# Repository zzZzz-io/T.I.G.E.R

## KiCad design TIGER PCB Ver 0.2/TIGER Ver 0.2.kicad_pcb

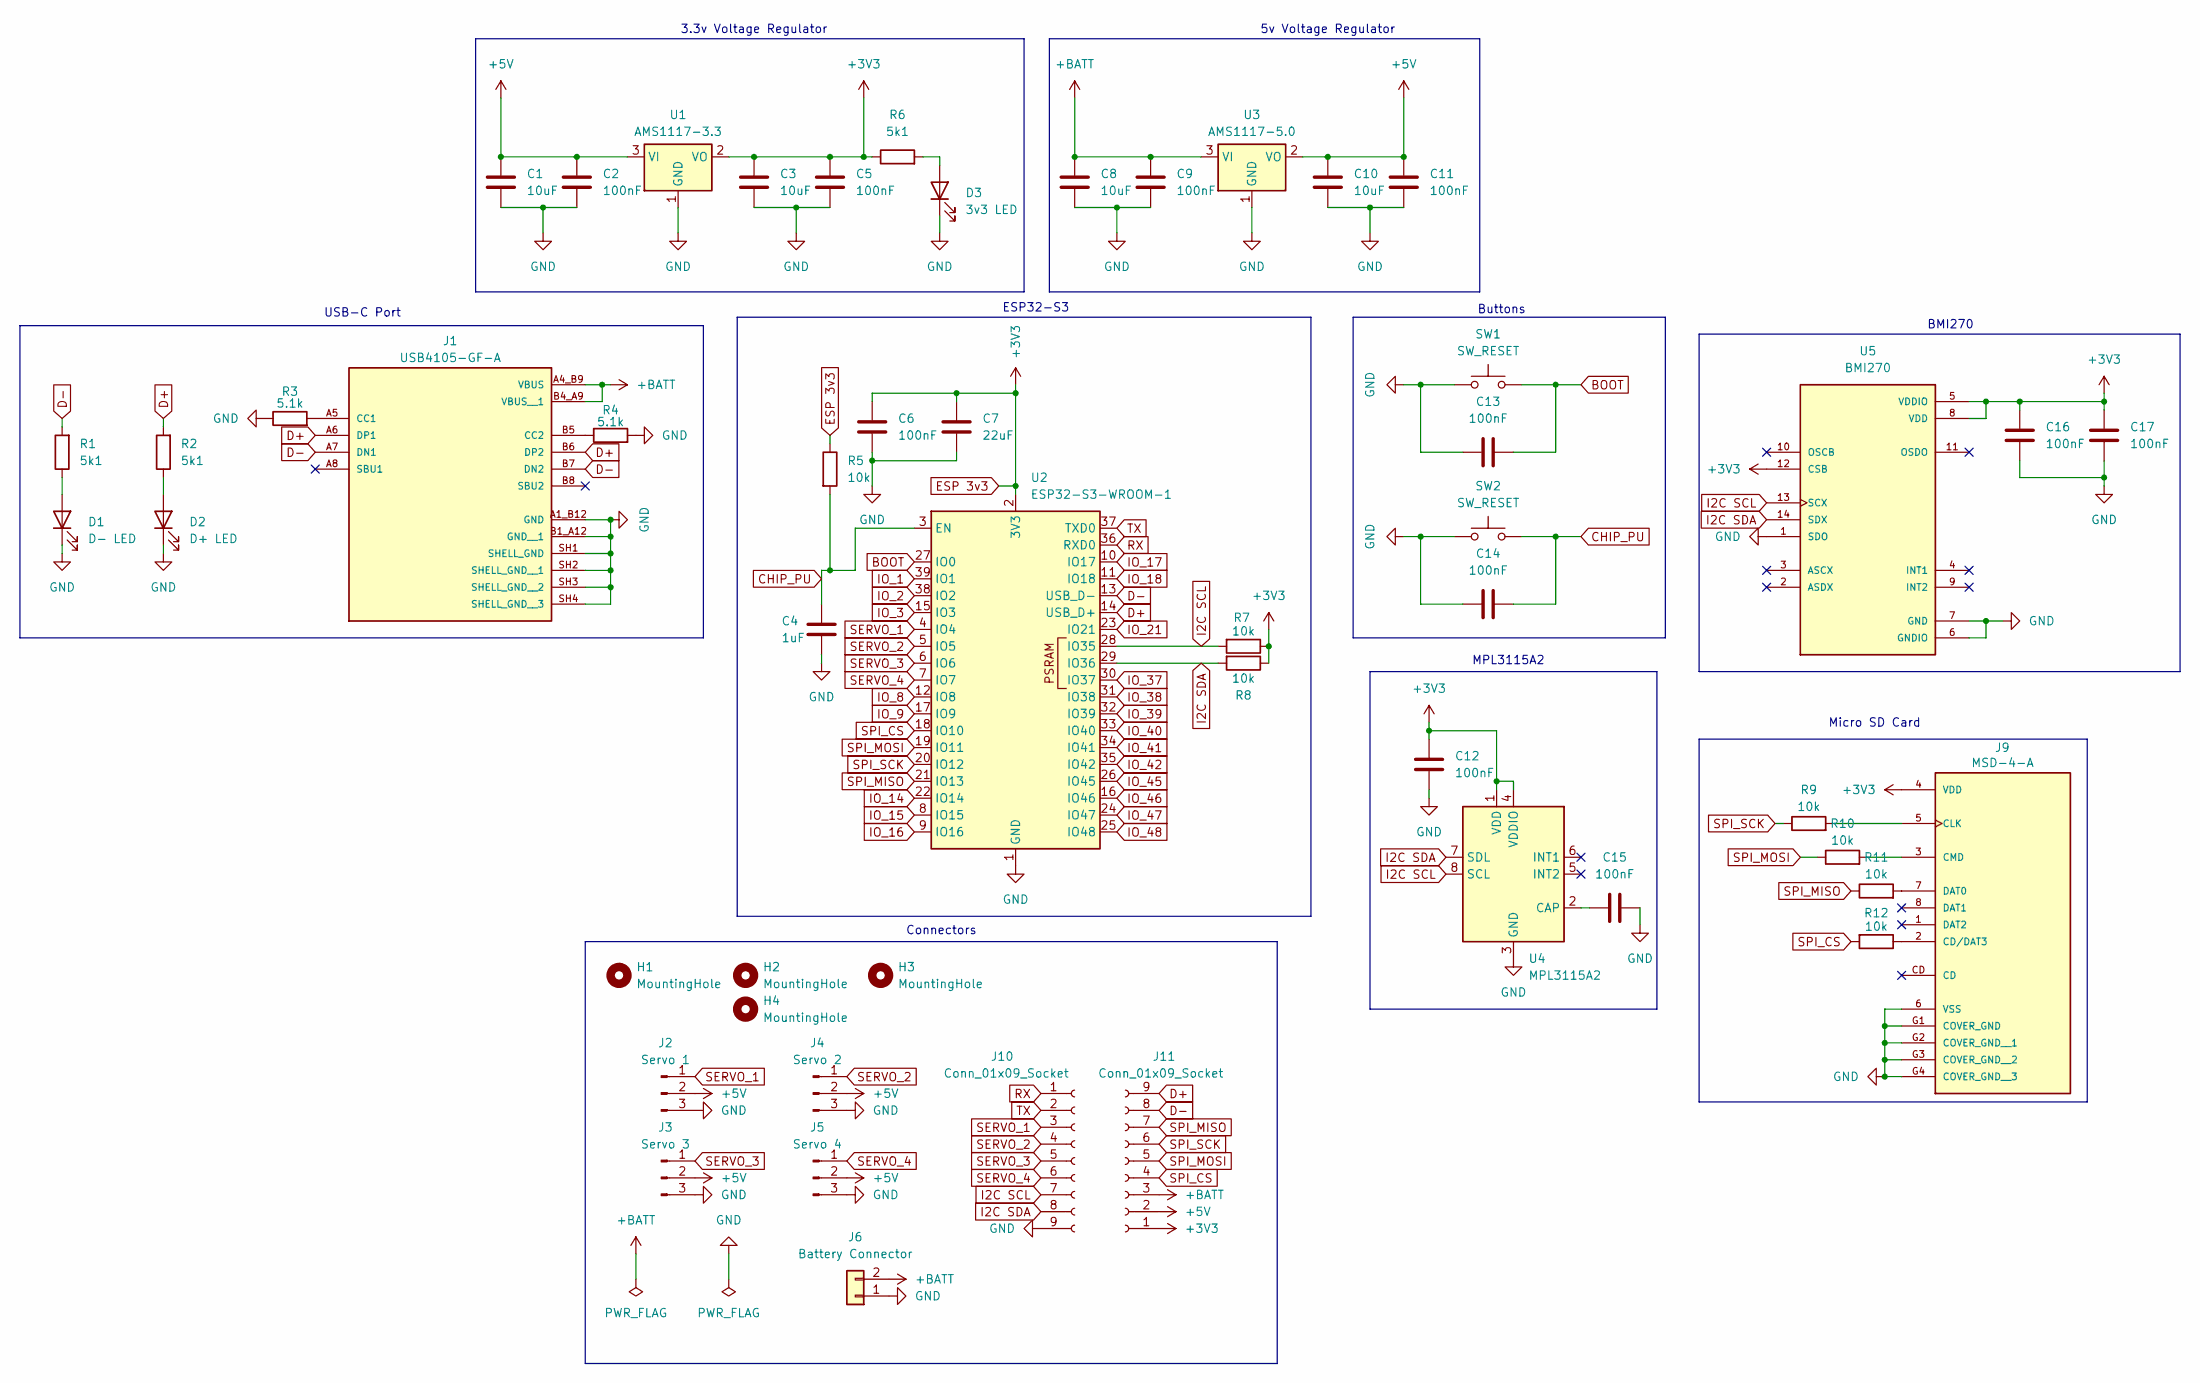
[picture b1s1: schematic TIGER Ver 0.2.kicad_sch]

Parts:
C1, C3, C8, C10: 10uF; C_0603_1608Metric
C2, C5, C6, C9, C11, C12, C13, C14, C15, C16, C17: 100nF; C_0603_1608Metric
C4: 1uF; C_0603_1608Metric
C7: 22uF; C_0603_1608Metric
D1: D- LED; LED_0603_1608Metric
D2: D+ LED; LED_0603_1608Metric
D3: 3v3 LED; LED_0603_1608Metric
H1, H2, H3, H4: MountingHole; MountingHole_3.2mm_M3
J1: USB4105-GF-A; GCT_USB4105-GF-A; PARTREV B4
J2: Servo 1; JST_PH_B3B-PH-K_1x03_P2.00mm_Vertical
J3: Servo 3; JST_PH_B3B-PH-K_1x03_P2.00mm_Vertical
J4: Servo 2; JST_PH_B3B-PH-K_1x03_P2.00mm_Vertical
J5: Servo 4; JST_PH_B3B-PH-K_1x03_P2.00mm_Vertical
J6: Battery Connector
J9: MSD-4-A; CUI_MSD-4-A; PARTREV 1.0
J10, J11: Conn_01x09_Socket; PinSocket_1x09_P2.54mm_Vertical
R1, R2, R6: 5k1; R_0603_1608Metric
R3, R4: 5.1k; R_0603_1608Metric
R5, R7, R8, R9, R10, R11, R12: 10k; R_0603_1608Metric
SW1, SW2: SW_RESET; SW_PUSH_6mm
U1: AMS1117-3.3; SOT-223-3_TabPin2
U2: ESP32-S3-WROOM-1
U3: AMS1117-5.0; SOT-223-3_TabPin2
U4: MPL3115A2; NXP_LGA-8_3x5mm_P1.25mm_H1.1mm
U5: BMI270; XDCR_BMI270

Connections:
+5V: C1.1, C2.1, C10.1, C11.1, J2.2, J3.2, J4.2, J5.2, J11.2, U1.3 (VI), U3.2 (VO)
+BATT: C8.1, C9.1, J1.A4_B9 (VBUS), J1.B4_A9 (VBUS__1), J6.2, J11.3, U3.3 (VI)
BOOT: C13.1, SW1.2, U2.27 (IO0)
CHIP_PU: C4.1, C14.1, R5.2, SW2.2, U2.3 (EN)
D+: J1.A6 (DP1), J1.B6 (DP2), J11.9, R2.2, U2.14 (USB_D+)
D-: J1.A7 (DN1), J1.B7 (DN2), J11.8, R1.2, U2.13 (USB_D-)
ESP 3v3: C3.1, C5.1, C6.1, C7.1, C12.2, C16.2, C17.1, J9.4 (VDD), J11.1, R5.1, R6.1, R7.1, R8.1, U1.2 (VO), U2.2 (3V3), U4.1 (VDD), U4.4 (VDDIO), U5.5 (VDDIO), U5.8 (VDD), U5.12 (CSB)
GND: C1.2, C2.2, C3.2, C4.2, C5.2, C6.2, C7.2, C8.2, C9.2, C10.2, C11.2, C12.1, C13.2, C14.2, C15.2, C16.1, C17.2, D1.1 (K), D2.1 (K), D3.1 (K), J1.A1_B12 (GND), J1.B1_A12 (GND__1), J1.SH1 (SHELL_GND), J1.SH2 (SHELL_GND__1), J1.SH3 (SHELL_GND__2), J1.SH4 (SHELL_GND__3), J2.3, J3.3, J4.3, J5.3, J6.1, J9.6 (VSS), J9.G1 (COVER_GND), J9.G2 (COVER_GND__1), J9.G3 (COVER_GND__2), J9.G4 (COVER_GND__3), J10.9, R3.1, R4.2, SW1.1, SW2.1, U1.1 (GND), U2.1 (GND), U2.40 (GND), U2.41 (GND), U3.1 (GND), U4.3 (GND), U5.1 (SDO), U5.6 (GNDIO), U5.7 (GND); also elsewhere on the board
I2C SCL: J10.7, R7.2, U2.28 (IO35), U4.8 (SCL), U5.13 (SCX)
I2C SDA: J10.8, R8.2, U2.29 (IO36), U4.7 (SDL), U5.14 (SDX)
IO_1: U2.39 (IO1)
IO_2: U2.38 (IO2)
IO_3: U2.15 (IO3)
IO_8: U2.12 (IO8)
IO_9: U2.17 (IO9)
IO_14: U2.22 (IO14)
IO_15: U2.8 (IO15)
IO_16: U2.9 (IO16)
IO_17: U2.10 (IO17)
IO_18: U2.11 (IO18)
IO_21: U2.23 (IO21)
IO_37: U2.30 (IO37)
IO_38: U2.31 (IO38)
IO_39: U2.32 (IO39)
IO_40: U2.33 (IO40)
IO_41: U2.34 (IO41)
IO_42: U2.35 (IO42)
IO_45: U2.26 (IO45)
IO_46: U2.16 (IO46)
IO_47: U2.24 (IO47)
IO_48: U2.25 (IO48)
unnamed: D1.2 (A), R1.1
unnamed: D2.2 (A), R2.1
unnamed 33: D3.2 (A), R6.2; also elsewhere on the board
unnamed: J1.A5 (CC1), R3.2
unnamed: J1.B5 (CC2), R4.1
unnamed: J9.2 (CD/DAT3), R12.1
unnamed: J9.5 (CLK), R9.2
unnamed: J9.3 (CMD), R10.2
unnamed: J9.7 (DAT0), R11.2
unnamed: C15.1, U4.2 (CAP)
RX: J10.1, U2.36 (RXD0)
SERVO_1: J2.1, J10.3, U2.4 (IO4)
SERVO_2: J4.1, J10.4, U2.5 (IO5)
SERVO_3: J3.1, J10.5, U2.6 (IO6)
SERVO_4: J5.1, J10.6, U2.7 (IO7)
SPI_CS: J11.4, R12.2, U2.18 (IO10)
SPI_MISO: J11.7, R11.1, U2.21 (IO13)
SPI_MOSI: J11.5, R10.1, U2.19 (IO11)
SPI_SCK: J11.6, R9.1, U2.20 (IO12)
TX: J10.2, U2.37 (TXD0)

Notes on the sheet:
Micro SD Card
Buttons
ESP32-S3
USB-C Port
3.3v Voltage Regulator
Connectors
5v Voltage Regulator
MPL3115A2
BMI270

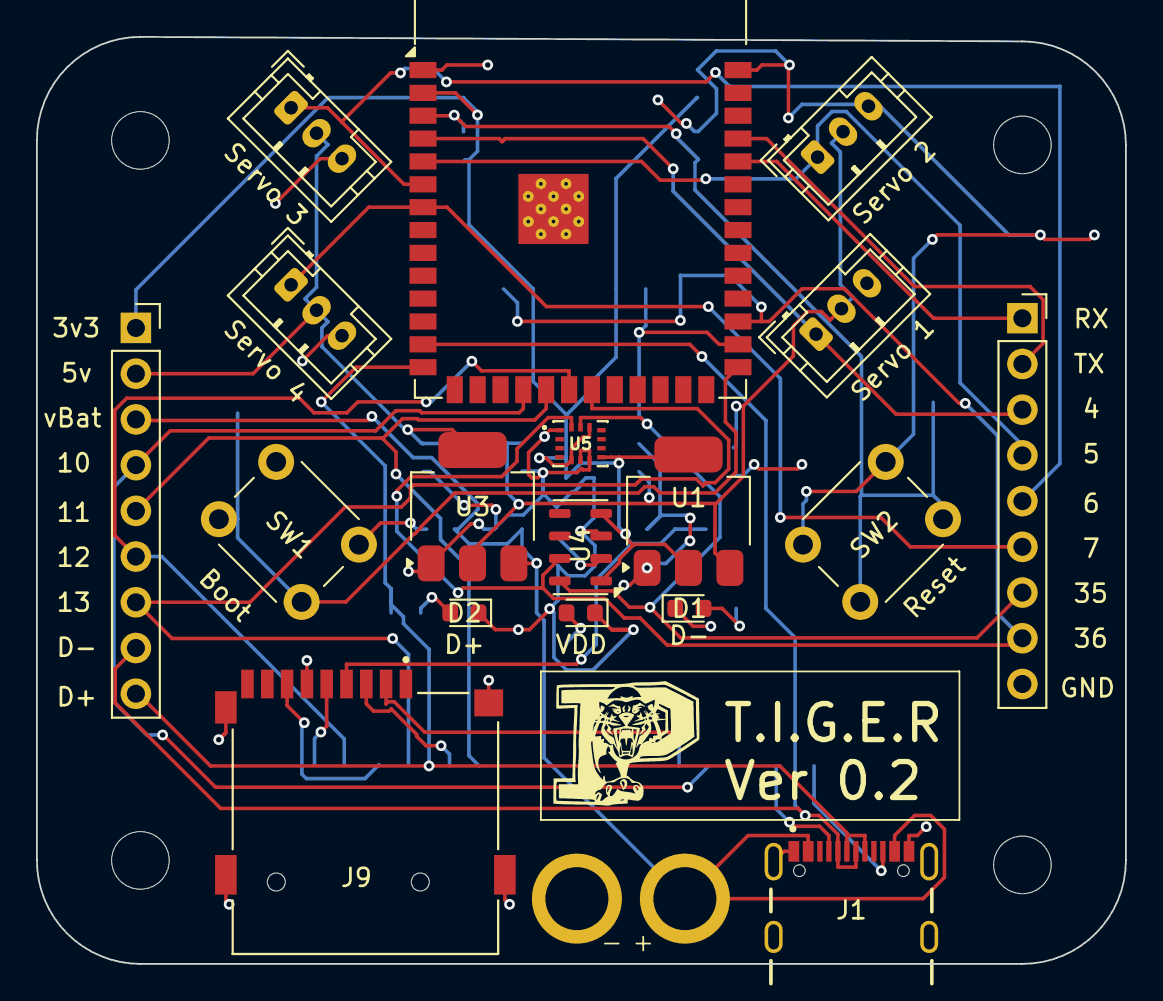
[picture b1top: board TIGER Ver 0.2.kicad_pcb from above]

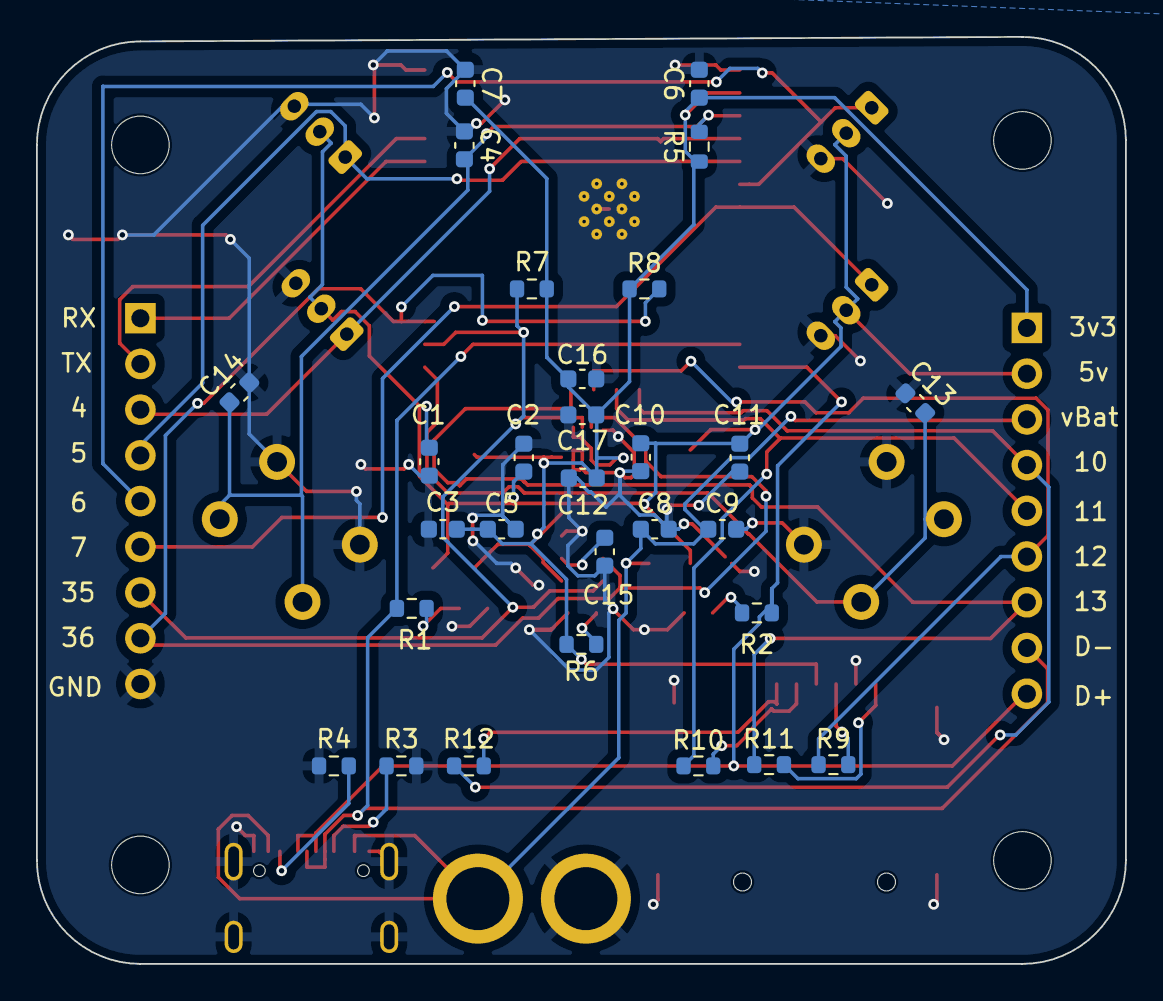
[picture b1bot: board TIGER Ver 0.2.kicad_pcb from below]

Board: 2 copper layers, 60.5 x 51.5 mm, 52 parts (29 on the bottom side), 30 nets.

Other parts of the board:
VDD: 3v3 LED; LED_0603_1608Metric

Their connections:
GND: VDD.1 (K); also elsewhere on the board
unnamed 33: VDD.2 (A); also elsewhere on the board

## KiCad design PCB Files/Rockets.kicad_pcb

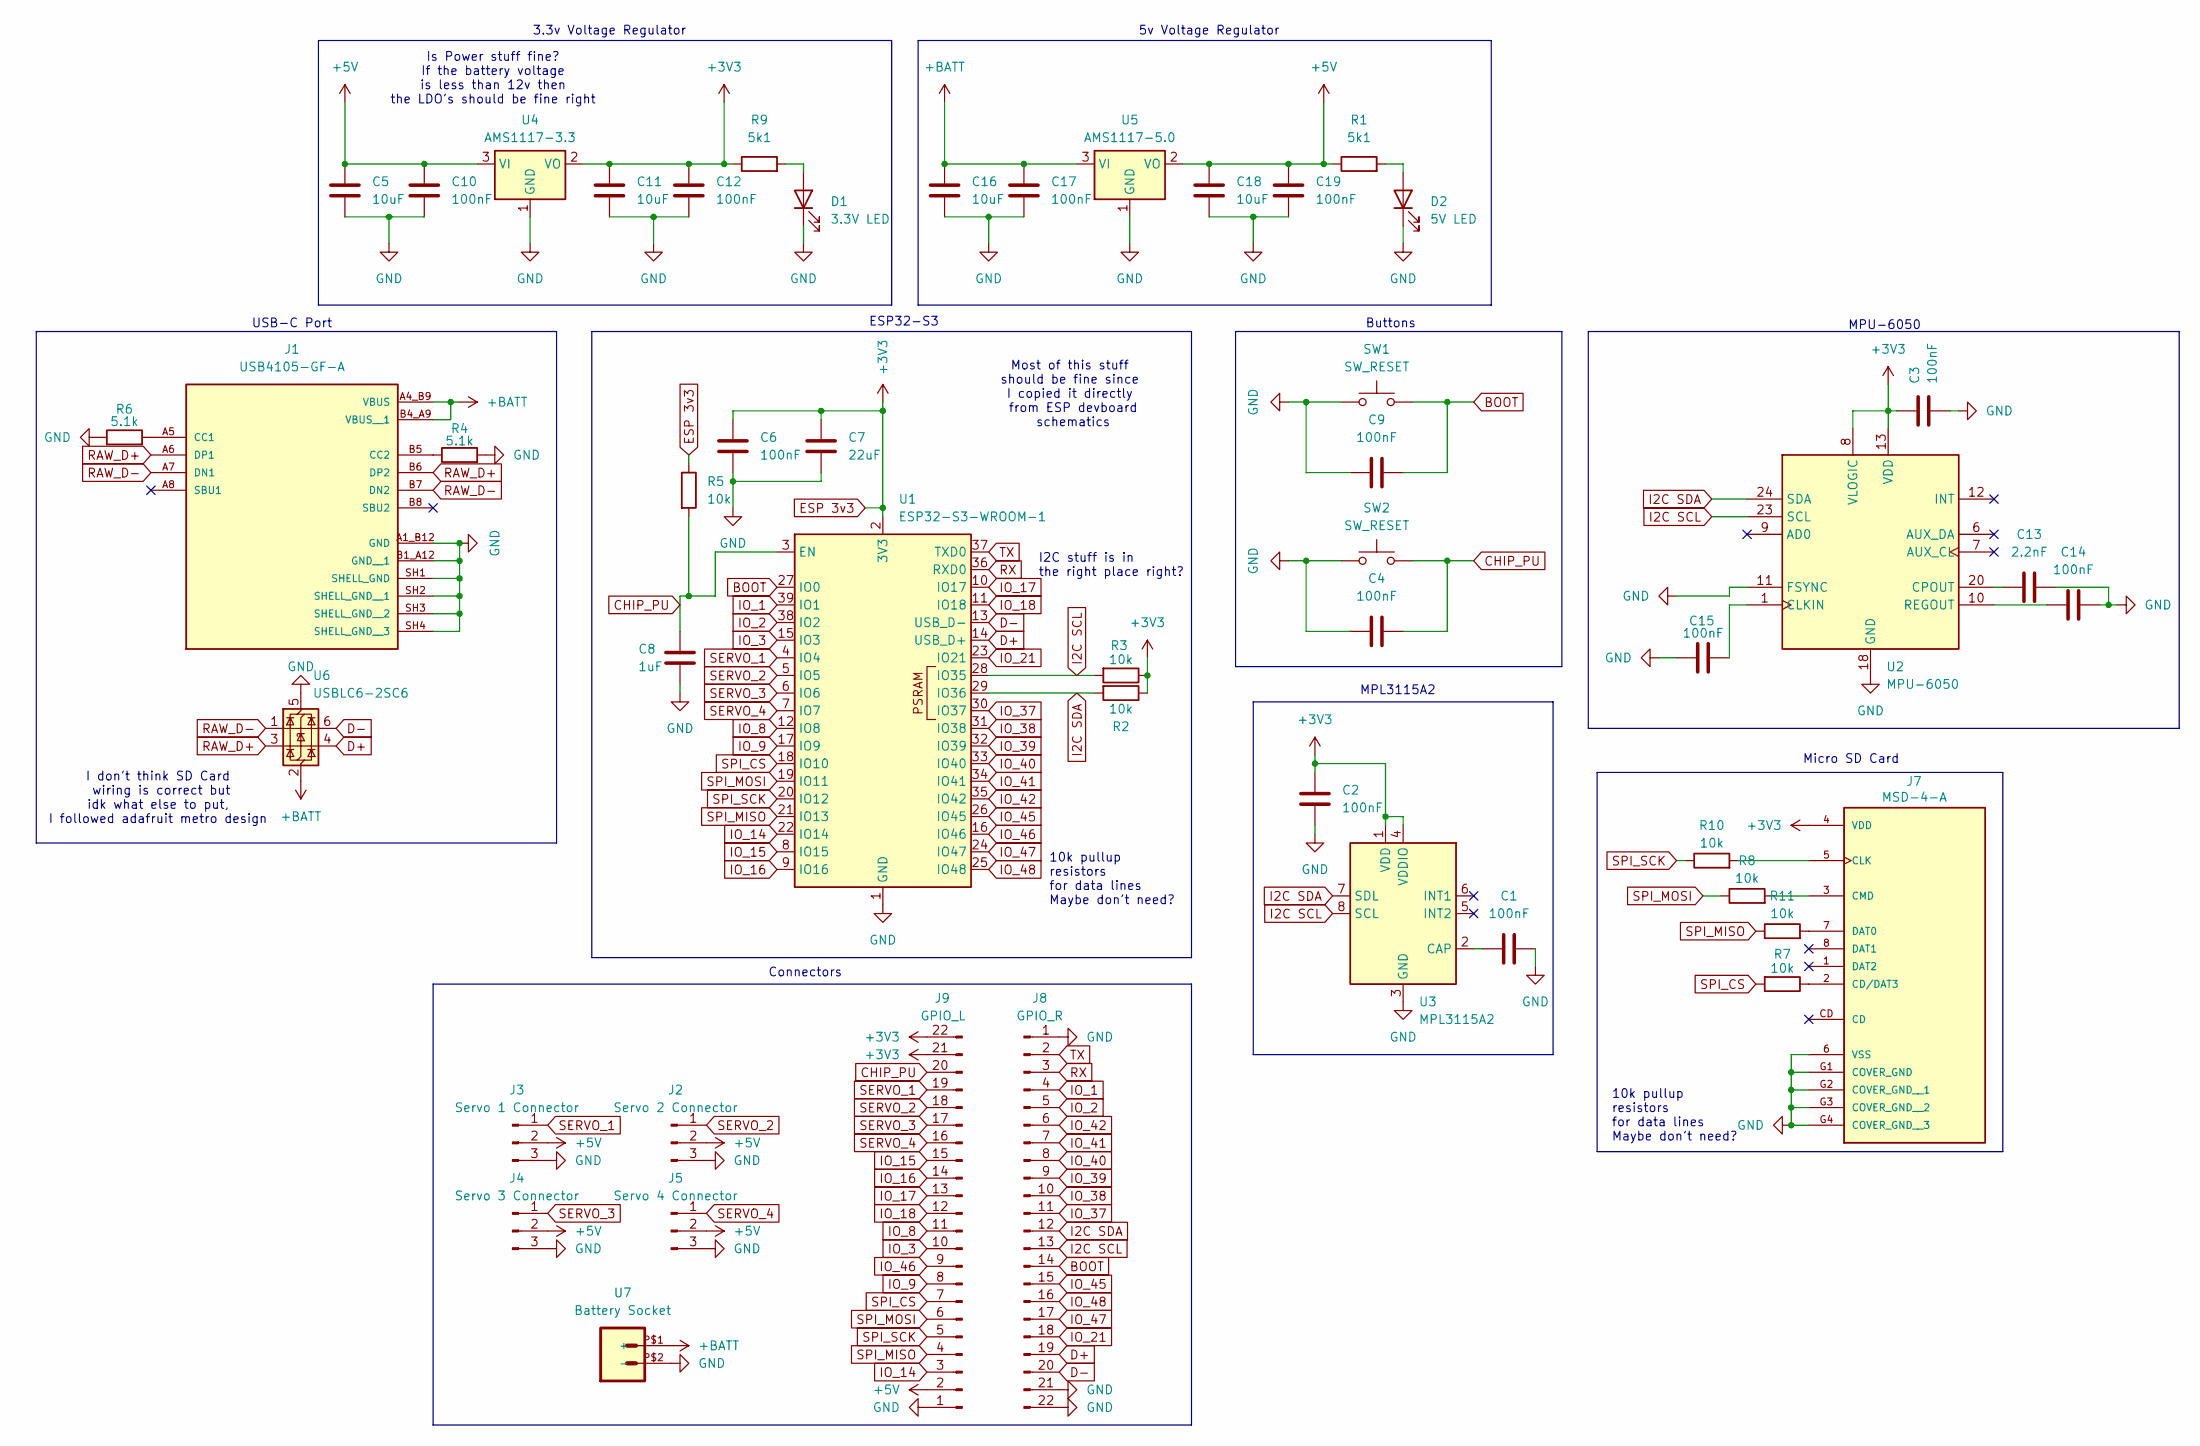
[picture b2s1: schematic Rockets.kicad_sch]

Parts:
C1, C2, C3, C4, C6, C9, C10, C12, C14, C15, C17, C19: 100nF; C_0603_1608Metric
C5, C11, C16, C18: 10uF; C_0603_1608Metric
C7: 22uF; C_0603_1608Metric
C8: 1uF; C_0603_1608Metric
C13: 2.2nF; C_0603_1608Metric
D1: 3.3V LED; LED_0603_1608Metric
D2: 5V LED; LED_0603_1608Metric
J1: USB4105-GF-A; GCT_USB4105-GF-A; PARTREV B4
J2: Servo 2 Connector; JST_PH_B3B-PH-K_1x03_P2.00mm_Vertical
J3: Servo 1 Connector; JST_PH_B3B-PH-K_1x03_P2.00mm_Vertical
J4: Servo 3 Connector; JST_PH_B3B-PH-K_1x03_P2.00mm_Vertical
J5: Servo 4 Connector; JST_PH_B3B-PH-K_1x03_P2.00mm_Vertical
J7: MSD-4-A; CUI_MSD-4-A; PARTREV 1.0
J8: GPIO_R; PinSocket_1x22_P2.54mm_Vertical
J9: GPIO_L; PinSocket_1x22_P2.54mm_Vertical
R1, R9: 5k1; R_0603_1608Metric
R2, R3, R5, R7, R8, R10, R11: 10k; R_0603_1608Metric
R4, R6: 5.1k; R_0603_1608Metric
SW1, SW2: SW_RESET; SW_PUSH_6mm
U1: ESP32-S3-WROOM-1
U2: MPU-6050; InvenSense_QFN-24_4x4mm_P0.5mm
U3: MPL3115A2; NXP_LGA-8_3x5mm_P1.25mm_H1.1mm
U4: AMS1117-3.3; SOT-223-3_TabPin2
U5: AMS1117-5.0; SOT-223-3_TabPin2
U6: USBLC6-2SC6; SOT-23-6
U7: Battery Socket; XT30UPB-M

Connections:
+5V: C5.1, C10.1, C18.1, C19.1, J2.2, J3.2, J4.2, J5.2, J9.2, R1.1, U4.3 (VI), U5.2 (VO)
+BATT: C16.1, C17.1, J1.A4_B9 (VBUS), J1.B4_A9 (VBUS__1), U5.3 (VI), U6.2 (GND), U7.P$1 (+)
BOOT: C9.1, J8.14, SW1.2, U1.27 (IO0)
CHIP_PU: C4.1, C8.1, J9.20, R5.2, SW2.2, U1.3 (EN)
D+: J8.19, U1.14 (USB_D+), U6.4 (I/O2)
D-: J8.20, U1.13 (USB_D-), U6.6 (I/O1)
ESP 3v3: C2.2, C3.1, C6.1, C7.1, C11.1, C12.1, J7.4 (VDD), J9.21, J9.22, R2.1, R3.1, R5.1, R9.1, U1.2 (3V3), U2.8 (VLOGIC), U2.13 (VDD), U3.1 (VDD), U3.4 (VDDIO), U4.2 (VO)
GND: C1.2, C2.1, C3.2, C4.2, C5.2, C6.2, C7.2, C8.2, C9.2, C10.2, C11.2, C12.2, C13.2, C14.2, C15.1, C16.2, C17.2, C18.2, C19.2, D1.1 (K), D2.1 (K), J1.A1_B12 (GND), J1.B1_A12 (GND__1), J1.SH1 (SHELL_GND), J1.SH2 (SHELL_GND__1), J1.SH3 (SHELL_GND__2), J1.SH4 (SHELL_GND__3), J2.3, J3.3, J4.3, J5.3, J7.6 (VSS), J7.G1 (COVER_GND), J7.G2 (COVER_GND__1), J7.G3 (COVER_GND__2), J7.G4 (COVER_GND__3), J8.1, J8.21, J8.22, J9.1, R4.2, R6.1, SW1.1, SW2.1, U1.1 (GND), U1.40 (GND), U1.41 (GND), U2.11 (FSYNC), U2.18 (GND), U3.3 (GND), U4.1 (GND), U5.1 (GND), U6.5 (VBUS), U7.P$2 (-); also elsewhere on the board
I2C SCL: J8.13, R3.2, U1.28 (IO35), U2.23 (SCL), U3.8 (SCL)
I2C SDA: J8.12, R2.2, U1.29 (IO36), U2.24 (SDA), U3.7 (SDL)
IO_1: J8.4, U1.39 (IO1)
IO_2: J8.5, U1.38 (IO2)
IO_3: J9.10, U1.15 (IO3)
IO_8: J9.11, U1.12 (IO8)
IO_9: J9.8, U1.17 (IO9)
IO_14: J9.3, U1.22 (IO14)
IO_15: J9.15, U1.8 (IO15)
IO_16: J9.14, U1.9 (IO16)
IO_17: J9.13, U1.10 (IO17)
IO_18: J9.12, U1.11 (IO18)
IO_21: J8.18, U1.23 (IO21)
IO_37: J8.11, U1.30 (IO37)
IO_38: J8.10, U1.31 (IO38)
IO_39: J8.9, U1.32 (IO39)
IO_40: J8.8, U1.33 (IO40)
IO_41: J8.7, U1.34 (IO41)
IO_42: J8.6, U1.35 (IO42)
IO_45: J8.15, U1.26 (IO45)
IO_46: J9.9, U1.16 (IO46)
IO_47: J8.17, U1.24 (IO47)
IO_48: J8.16, U1.25 (IO48)
unnamed 31: D1.2 (A), R9.2; also elsewhere on the board
unnamed 32: D2.2 (A), R1.2; also elsewhere on the board
unnamed: J1.A5 (CC1), R6.2
unnamed: J1.B5 (CC2), R4.1
unnamed: J7.2 (CD/DAT3), R7.1
unnamed: J7.5 (CLK), R10.2
unnamed: J7.3 (CMD), R8.2
unnamed: J7.7 (DAT0), R11.2
unnamed: C15.2, U2.1 (CLKIN)
unnamed: C13.1, U2.20 (CPOUT)
unnamed: C14.1, U2.10 (REGOUT)
unnamed: C1.1, U3.2 (CAP)
RAW_D+: J1.A6 (DP1), J1.B6 (DP2), U6.3 (I/O2)
RAW_D-: J1.A7 (DN1), J1.B7 (DN2), U6.1 (I/O1)
RX: J8.3, U1.36 (RXD0)
SERVO_1: J3.1, J9.19, U1.4 (IO4)
SERVO_2: J2.1, J9.18, U1.5 (IO5)
SERVO_3: J4.1, J9.17, U1.6 (IO6)
SERVO_4: J5.1, J9.16, U1.7 (IO7)
SPI_CS: J9.7, R7.2, U1.18 (IO10)
SPI_MISO: J9.4, R11.1, U1.21 (IO13)
SPI_MOSI: J9.6, R8.1, U1.19 (IO11)
SPI_SCK: J9.5, R10.1, U1.20 (IO12)
TX: J8.2, U1.37 (TXD0)

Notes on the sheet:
Micro SD Card
Buttons
ESP32-S3
I2C stuff is in the right place right?
USB-C Port
I don't think SD Card wiring is correct but idk what else to put, I followed adafruit metro design
Most of this stuff should be fine since I copied it directly from ESP devboard schematics
3.3v Voltage Regulator
Connectors
5v Voltage Regulator
10k pullup resistors for data lines Maybe don't need?
MPU-6050
MPL3115A2
Is Power stuff fine? If the battery voltage is less than 12v then the LDO's should be fine right

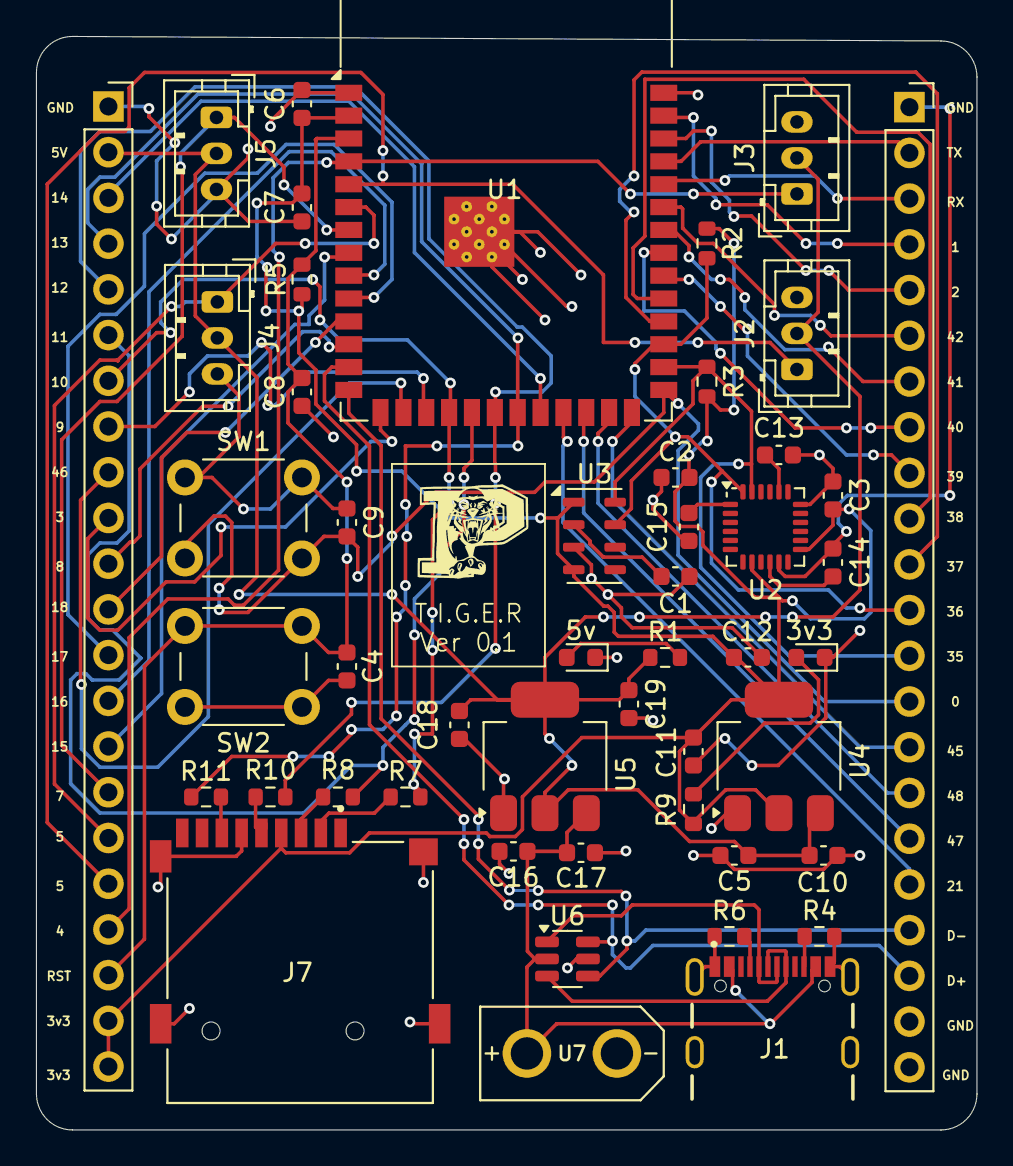
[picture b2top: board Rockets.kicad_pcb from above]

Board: 2 copper layers, 52.2 x 60.8 mm, 49 parts (0 on the bottom side), 55 nets.

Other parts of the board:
3v3: 3.3V LED; LED_0603_1608Metric
5v: 5V LED; LED_0603_1608Metric

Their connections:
GND: 3v3.1 (K), 5v.1 (K); also elsewhere on the board
unnamed 31: 3v3.2 (A); also elsewhere on the board
unnamed 32: 5v.2 (A); also elsewhere on the board

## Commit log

2025-04-23 v0.1
2025-04-23 PID progress
    TIGER Pid Code 4/23/25
2025-04-28 PCB Files
2025-04-30 wasd
2025-04-30 PI working
2025-05-02 TigerCodeMay2
    With explanations
2025-05-02 Wifi Test
2025-06-12 Idk what I changed but we'll update it
2025-06-12 Making Ver 0.2 Files
2025-06-23 Again
2025-06-23 lalala
2025-06-23 More progress
2025-06-24 Layout almost done
2025-06-24 Finished Layout
2025-06-24 Ver 0.2 Completed
2025-06-26 TIGER Ver 0.2 Final
2025-07-04 Ok actual final
